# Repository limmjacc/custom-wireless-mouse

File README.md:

# custom-wireless-mouse

Custom BLE wireless mouse: from-scratch PCB (KiCad) and firmware (nRF
Connect SDK / Zephyr) built to fit the mechanical envelope of the Bambu
Lab-style "Wireless Mouse Components Kit-002" (MH002), replacing its two
undocumented/discontinued ICs with fully public, sourceable parts.

See [docs/hardware/README.md](docs/hardware/README.md) for the full design
rationale, bill of materials, and net list, and
[docs/firmware/README.md](docs/firmware/README.md) for firmware scope.

## Layout

```
.
├── hardware/     KiCad 10 project — schematic, PCB layout, libraries
├── firmware/     nRF Connect SDK (Zephyr) application
├── docs/         Design documentation (hardware and firmware)
└── mechanical/   Notes on the reused kit mechanical parts
```

## Status

Schematic complete and ERC-verified (see [docs/hardware/schematic.md](docs/hardware/schematic.md)).
PCB layout not yet started, not built, not tested. No firmware logic has
been written. See each section's open-items document for what's left.

## Credits

Every vendored KiCad library part under `hardware/libraries/vendored/`
carries its own `ATTRIBUTION.md` with full sourcing detail. The two with
licenses other than KiCad's own (CC-BY-SA 4.0, used simply because most
parts were extracted from KiCad's or DigiKey's official libraries):

- The PMW3610DM-SUDU sensor's symbol and footprint, at
  [`hardware/libraries/vendored/pmw3610dm-sudu/`](hardware/libraries/vendored/pmw3610dm-sudu/),
  are from [**siderakb/pmw3610-pcb**](https://github.com/siderakb/pmw3610-pcb),
  an open-hardware PMW3610 breakout board by **siderakb**, licensed under the
  CERN Open Hardware Licence v2 — Permissive (CERN-OHL-P v2).
- The PEC11R rotary encoder footprint and the JS202011SCQN slide switch
  footprint, at
  [`hardware/libraries/vendored/bourns-pec11r/`](hardware/libraries/vendored/bourns-pec11r/)
  and
  [`hardware/libraries/vendored/ck-js202011scqn/`](hardware/libraries/vendored/ck-js202011scqn/),
  are from [**Digi-Key's official KiCad library**](https://github.com/Digi-Key/digikey-kicad-library)
  (CC-BY-SA 4.0).

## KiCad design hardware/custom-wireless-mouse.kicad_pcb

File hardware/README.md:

# Hardware

KiCad 10 project for the custom wireless mouse PCB. Fully self-contained and
portable: every symbol, footprint, and 3D model the schematic depends on is
vendored inside this folder and referenced through `${KIPRJMOD}`-relative
paths — nothing depends on KiCad's global library tables or an internet
connection to open and edit. See [`docs/hardware/schematic.md`](../docs/hardware/schematic.md)
for how the schematic itself is organized.

## Opening the project

Open `custom-wireless-mouse.kicad_pro` in KiCad 10. The project's
`sym-lib-table` and `fp-lib-table` are picked up automatically.

## Layout

```
hardware/
├── custom-wireless-mouse.kicad_pro   Project file
├── custom-wireless-mouse.kicad_sch   Schematic — complete, ERC-clean
├── custom-wireless-mouse.kicad_pcb   PCB layout — not started (no board outline yet)
├── sym-lib-table                     Project-local symbol library table
├── fp-lib-table                      Project-local footprint library table
├── datasheets/                       PDF datasheets for every non-passive part, kebab-case named
├── libraries/
│   ├── local/                        Symbols/footprints authored for this project
│   │   └── symbols/local.kicad_sym     GND, +VSYS, and PWR_FLAG
│   └── vendored/                     One directory per part, each with its own ATTRIBUTION.md
│       ├── nordic-nrf52810-qcxx/       U1 — from KiCad's own official library
│       ├── pmw3610dm-sudu/             U2 — from github.com/siderakb/pmw3610-pcb (CERN-OHL-P v2)
│       ├── ti-tlv61220/                U3 — symbol hand-drawn from TI's datasheet pinout
│       ├── ndk-nx2016sa/               Y1 — from KiCad's own official library
│       ├── bourns-pec11r/              ENC1 — from DigiKey's official KiCad library
│       ├── panasonic-evq-p7b01p/       SW2–SW4 — from KiCad's own official library
│       ├── ck-js202011scqn/            SW1 — from DigiKey's official KiCad library
│       └── samtec-tsw-104-07-t-s/      J1 — from KiCad's own official library
├── fab-outputs/                      Gerbers, drill, pick-and-place, and BOM exports per revision
└── 3d-renders/                       Exported board renders (PNG/STEP) for docs and reference
```

## Library policy

Every specific, individually sourced part (every IC, the crystal, the
encoder, every switch, the header) has its own symbol and footprint vendored
into `libraries/vendored/<part>/` — nothing depends on KiCad's global
libraries for these, since a global library's contents can differ across
KiCad installs and versions. Only truly generic, manufacturer-agnostic
passives (resistors, capacitors, the inductor) use KiCad's bundled `Device`
and footprint libraries directly, since there's no meaningful "sourcing"
decision attached to a 0603 resistor footprint.

Each vendored part's `ATTRIBUTION.md` records exactly where its symbol and
footprint came from and what license applies (mostly CC-BY-SA 4.0, matching
KiCad's own library license, since most of these were extracted from KiCad's
or DigiKey's official libraries; U2 is CERN-OHL-P v2 from its open-hardware
source; U3's symbol is original, hand-drawn from a public datasheet pinout
table rather than copied from anywhere).

## Datasheets

`datasheets/` holds a PDF for every part above the passive-component level —
downloaded from the manufacturer or a stable distributor mirror where a
direct link could be found. A couple of manufacturers' sites (Nordic's full
product specification, one slide-switch datasheet) sit behind bot-protection
that blocked a direct download; where that happened, the BOM notes it and
gives the page to fetch manually instead of a broken/substituted link.

## Fabrication outputs

`fab-outputs/` holds exports generated *from* the KiCad project (Gerbers,
drill files, pick-and-place, BOM) — never hand-edited. Regenerate per
revision; don't rely on stale exports. Nothing has been exported yet since
the PCB layout hasn't started.

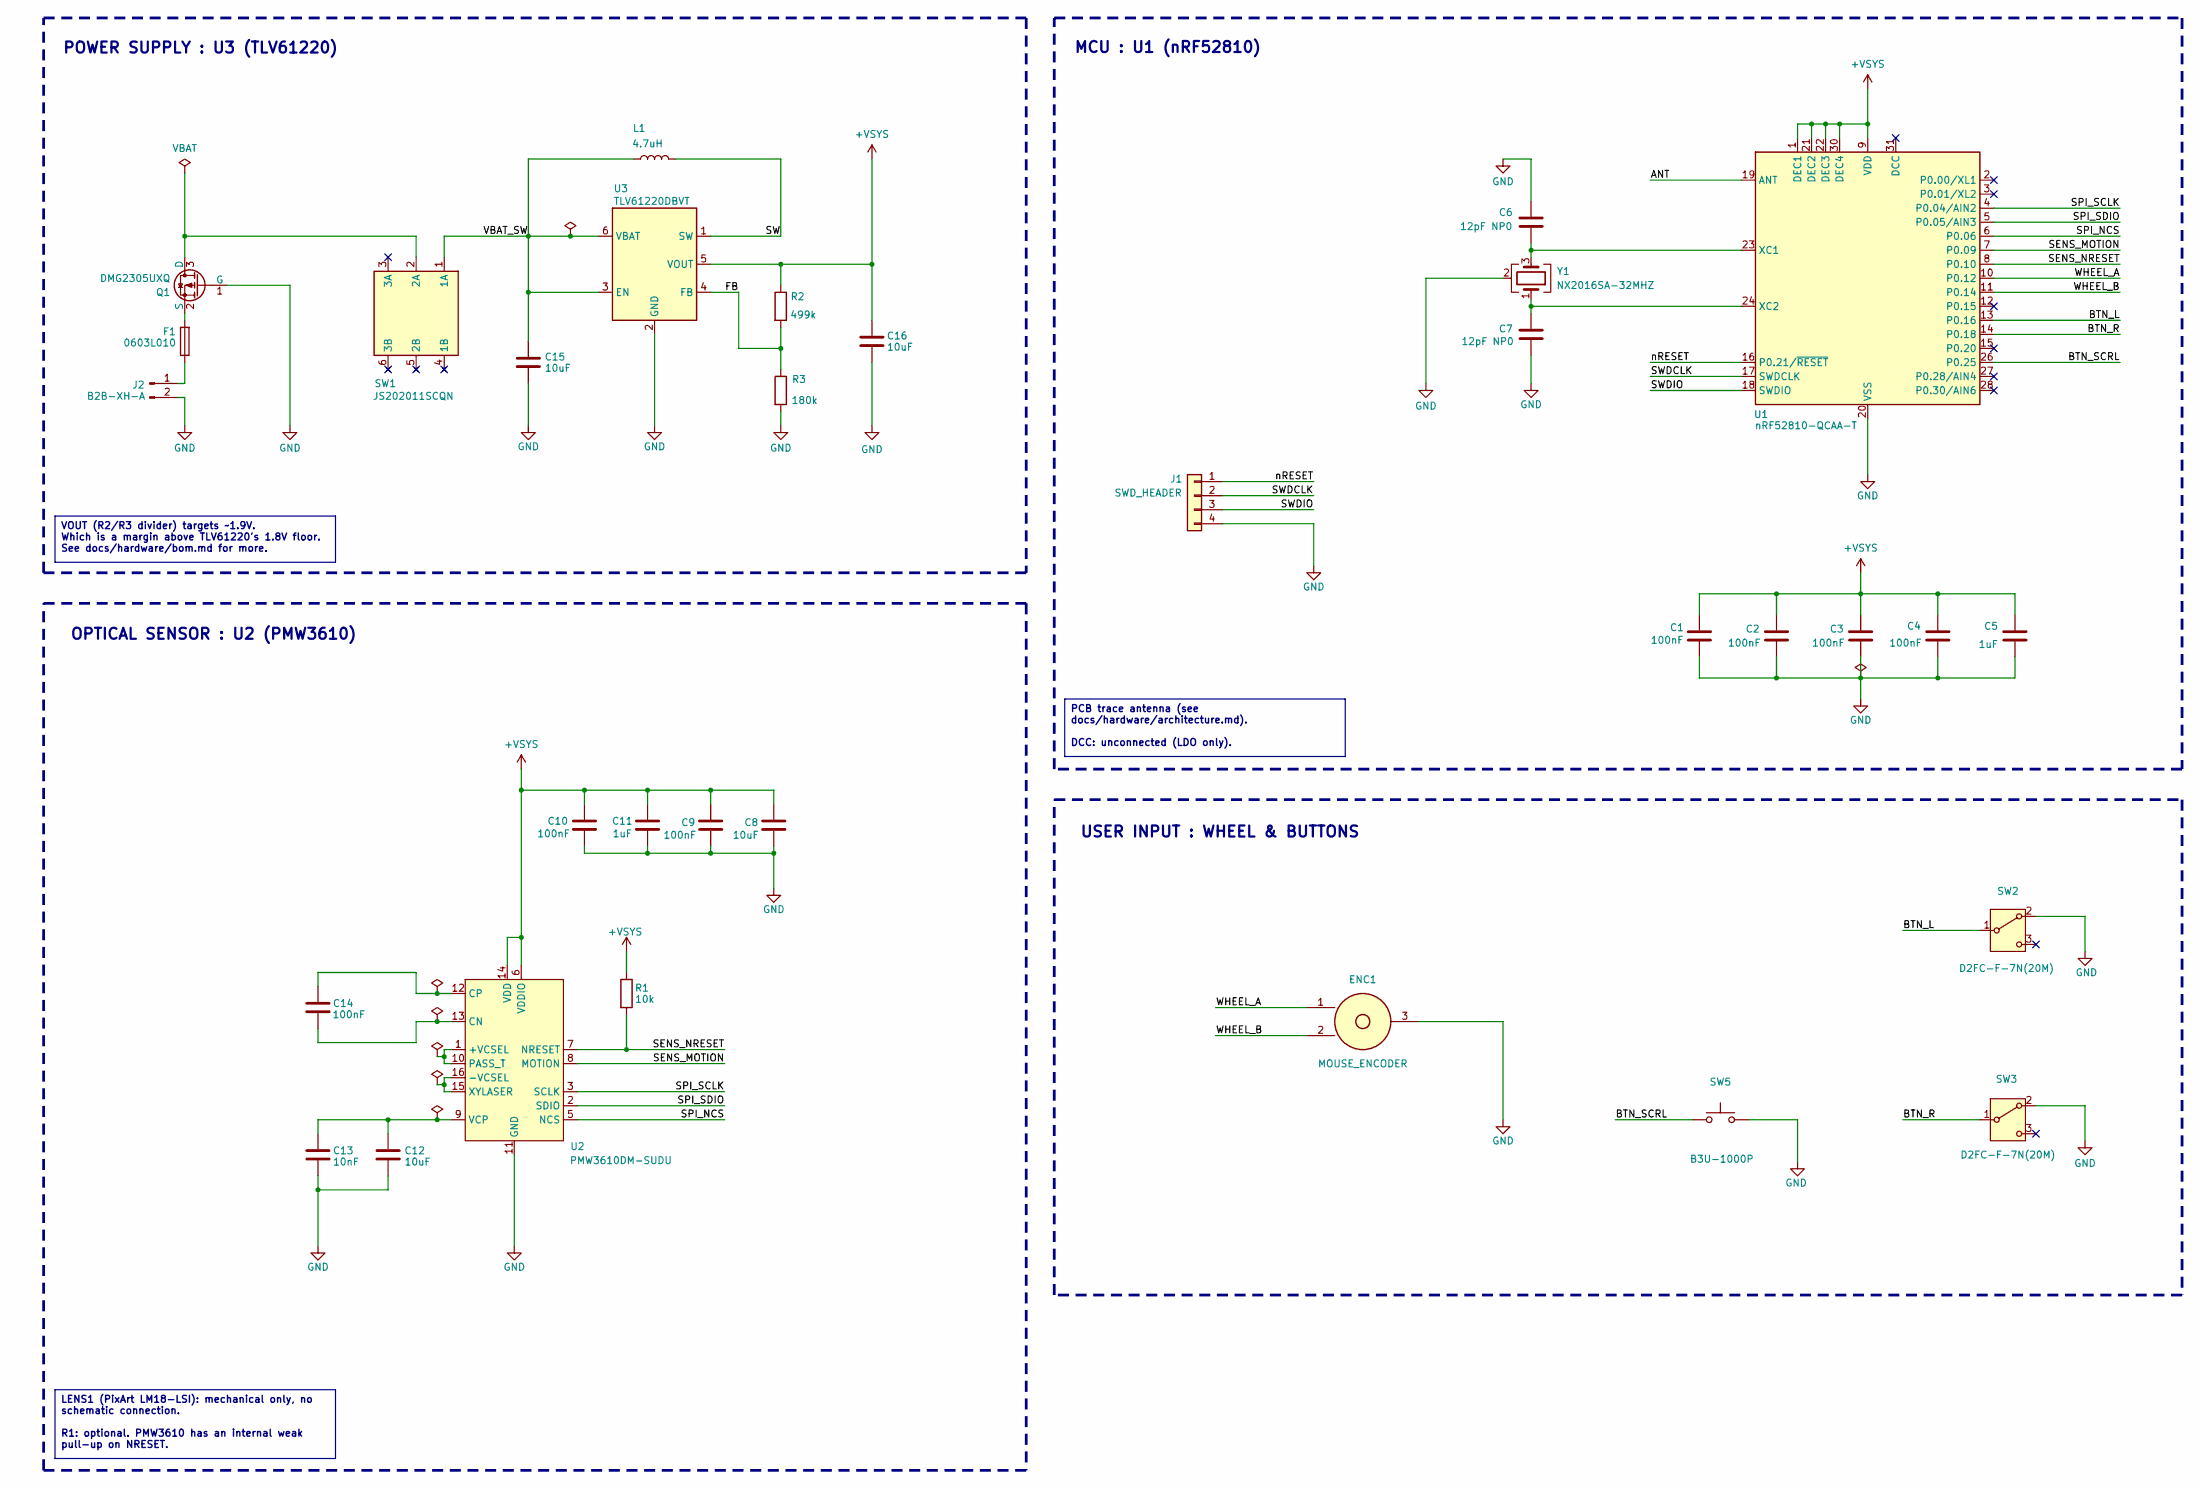
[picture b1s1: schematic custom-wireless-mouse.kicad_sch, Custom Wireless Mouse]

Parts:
C1, C2, C3, C4, C9, C10, C14: 100nF; C_0603_1608Metric; MPN CC0603KRX7R9BB104
C5, C11: 1uF; C_0603_1608Metric; MPN CC0603KRX5R6BB105
C6, C7: 12pF NP0; C_0402_1005Metric; MPN CC0402FRNPO9BN120
C8, C12, C15, C16: 10uF; C_0603_1608Metric; MPN GRT188R61A106KE13J
C13: 10nF; C_0603_1608Metric; MPN CC0603KRX7R9BB103
ENC1: MOUSE_ENCODER; encoder-tht-placeholder-mouse-wheel; MPN Mouse scroll encoder, 7-9mm body height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
F1: 0603L010; fuse-0603-littelfuse-0603l010; MPN 0603L010YR
J1: SWD_HEADER; pinheader-1x04-p2.54mm-vertical; MPN TSW-104-07-T-S
J2: B2B-XH-A; battery-conn-jst-b2b-xh-a; MPN B2B-XH-A(LF)(SN)
L1: 4.7uH; L_1008_2520Metric; MPN 1269AS-H-4R7M=P2
Q1: DMG2305UXQ; sot-23-dmg2305uxq; MPN DMG2305UXQ-7
R1: 10k; R_0603_1608Metric; MPN RC0603FR-0710KL
R2: 499k; R_0603_1608Metric; MPN RC0603FR-07499KL
R3: 180k; R_0603_1608Metric; MPN RC0603FR-07180KL
SW1: JS202011SCQN; switch-slide-js202011scqn; MPN JS202011SCQN
SW2, SW3: D2FC-F-7N(20M); switch-tht-omron-d2fc-f-7n; MPN D2FC-F-7N(20M)
SW5: B3U-1000P; switch-smd-omron-b3u-1000p; MPN B3U-1000P
U1: nRF52810-QCAA-T; qfn-32-1ep-5x5mm-p0.5mm-ep3.6x3.6mm; MPN nRF52810-QCAA-T
U2: PMW3610DM-SUDU; pmw3610dm-sudu-16-pin; MPN PMW3610DM-SUDU
U3: TLV61220DBVT; sot-23-6; MPN TLV61220DBVT
Y1: NX2016SA-32MHZ; crystal-smd-2016-4pin-2.0x1.6mm; MPN NX2016SA-32MHZ-EXS00A-CS06654

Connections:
+VSYS: C1.1, C2.1, C3.1, C4.1, C5.1, C8.1, C9.1, C10.1, C11.1, C16.1, R1.1, R2.1, U1.1 (DEC1), U1.9 (VDD), U1.21 (DEC2), U1.22 (DEC3), U1.25 (VDD), U1.30 (DEC4), U1.32 (VDD), U2.6 (VDDIO), U2.14 (VDD), U3.5 (VOUT)
/ANT: U1.19 (ANT)
/BTN_L: SW2.1 (COM), U1.13 (P0.16)
/BTN_R: SW3.1 (COM), U1.14 (P0.18)
/BTN_SCRL: SW5.1, U1.26 (P0.25)
/FB: R2.2, R3.1, U3.4 (FB)
/SENS_MOTION: U1.7 (P0.09), U2.8 (MOTION)
/SENS_NRESET: R1.2, U1.8 (P0.10), U2.7 (NRESET)
/SPI_NCS: U1.6 (P0.06), U2.5 (NCS)
/SPI_SCLK: U1.4 (P0.04/AIN2), U2.3 (SCLK)
/SPI_SDIO: U1.5 (P0.05/AIN3), U2.2 (SDIO)
/SW: L1.2, U3.1 (SW)
/SWDCLK: J1.2 (SWDCLK), U1.17 (SWDCLK)
/SWDIO: J1.3 (GND), U1.18 (SWDIO)
/VBAT_SW: C15.1, L1.1, SW1.1 (1A), U3.3 (EN), U3.6 (VBAT)
/WHEEL_A: ENC1.1 (A), U1.10 (P0.12)
/WHEEL_B: ENC1.2 (B), U1.11 (P0.14)
/nRESET: J1.1 (SWDIO), U1.16 (P0.21/~RESET)
GND: C1.2, C2.2, C3.2, C4.2, C5.2, C6.1, C7.2, C8.2, C9.2, C10.2, C11.2, C12.2, C13.2, C15.2, C16.2, ENC1.3 (COM), J1.4 (~RESET), J2.2 (-), Q1.1 (G), R3.2, SW2.2 (NO), SW3.2 (NO), SW5.2, U1.20 (VSS), U1.29 (VSS), U1.33 (VSS), U2.11 (GND), U3.2 (GND), Y1.2 (G), Y1.4 (G)
unnamed: F1.1, J2.1 (+)
unnamed: Q1.3 (D), SW1.2 (2A)
unnamed: F1.2, Q1.2 (S)
unnamed: C6.2, U1.23 (XC1), Y1.3
unnamed: C7.1, U1.24 (XC2), Y1.1
unnamed: U2.1 (+VCSEL), U2.10 (PASS_T)
unnamed: U2.15 (XYLASER), U2.16 (-VCSEL)
unnamed: C14.2, U2.13 (CN)
unnamed: C14.1, U2.12 (CP)
unnamed: C12.1, C13.1, U2.9 (VCP)

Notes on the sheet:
USER INPUT : WHEEL & BUTTONS
POWER SUPPLY : U3 (TLV61220)
MCU : U1 (nRF52810)
OPTICAL SENSOR : U2 (PMW3610)
LENS1 (PixArt LM18-LSI): mechanical only, no schematic connection. R1: optional. PMW3610 has an internal weak pull-up on NRESET.
PCB trace antenna (see docs/hardware/architecture.md). DCC: unconnected (LDO only).
VOUT (R2/R3 divider) targets ~1.9V. Which is a margin above TLV61220's 1.8V floor. See docs/hardware/bom.md for more.

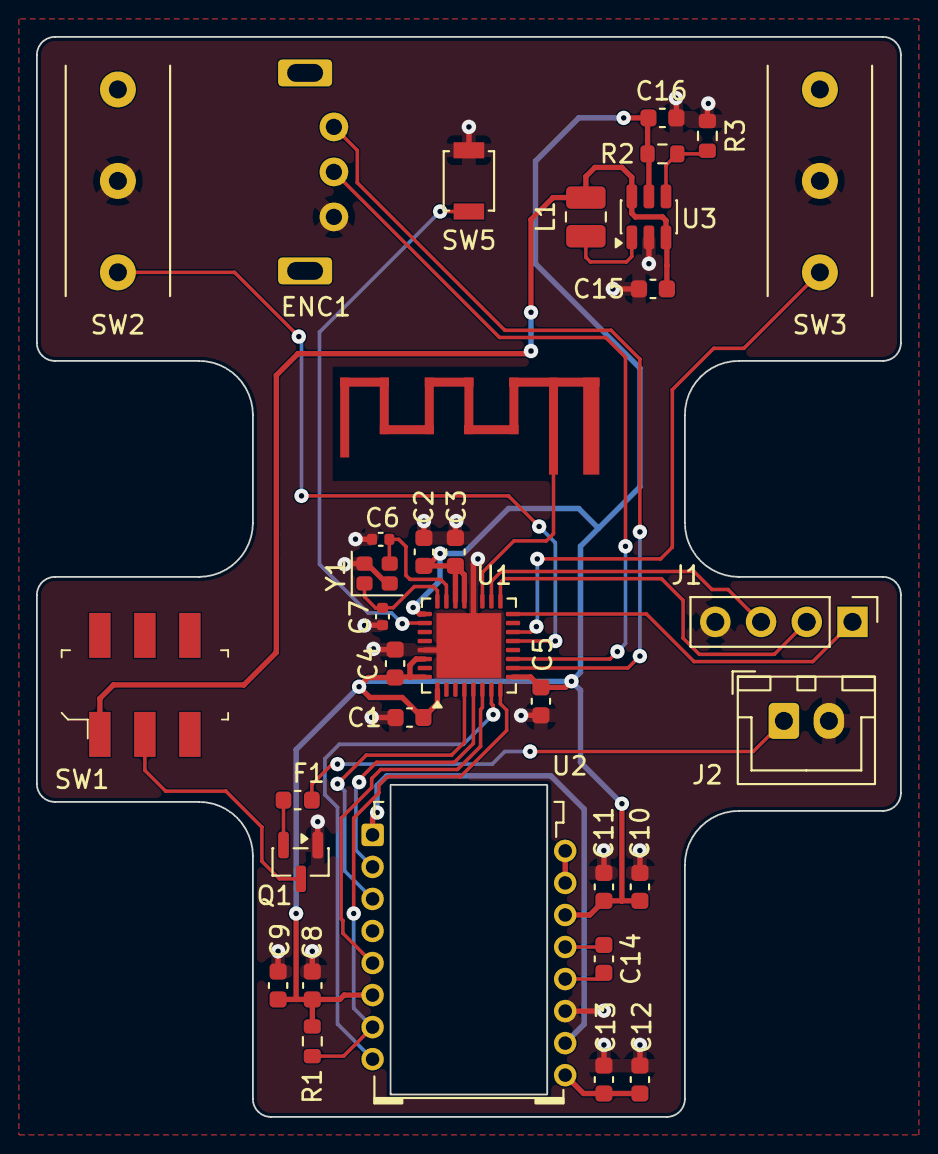
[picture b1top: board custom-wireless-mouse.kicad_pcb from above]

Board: 2 copper layers, 48.0 x 60.0 mm, 33 parts (0 on the bottom side), 28 nets.

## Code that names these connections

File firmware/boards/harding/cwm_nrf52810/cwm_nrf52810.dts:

/*
 * SPDX-License-Identifier: Apache-2.0
 *
 * Board definition for the custom wireless mouse PCB (U1: nRF52810, 32-QFN
 * 5x5mm package). See docs/hardware/ for the full electrical design this
 * board file targets, in particular pinout.md and open-items.md — several
 * peripheral nodes below are deliberately left unassigned pending the GPIO
 * pin assignment open item.
 */

/dts-v1/;
#include <nordic/nrf52810_qfaa.dtsi>
#include "cwm_nrf52810-pinctrl.dtsi"

/ {
	model = "Custom Wireless Mouse (nRF52810)";
	compatible = "harding,cwm-nrf52810";

	chosen {
		zephyr,sram = &sram0;
		zephyr,flash = &flash0;
	};

	/*
	 * Not yet defined here, pending pin assignment
	 * (docs/hardware/open-items.md, item 5):
	 *
	 *   - spi1: bus to U2 (PMW3610), pinctrl for SCLK/SDIO/NCS
	 *     (docs/hardware/pinout.md, U1 section)
	 *   - gpio-keys: BTN_L (SW2), BTN_R (SW3), BTN_FN (SW4), WHEEL_SW
	 *   - PMW3610 MOTION line as a GPIO interrupt input
	 *   - WHEEL_A / WHEEL_B quadrature inputs for ENC1
	 *
	 * Add these once layout fixes the P0.xx assignment for each signal.
	 */
};

/*
 * P0.21 doubles as the SWD RESET line (J1) per
 * docs/hardware/pinout.md — configure it as external reset rather than a
 * general-purpose GPIO.
 */
&uicr {
	gpio-as-nreset;
};

&gpiote {
	status = "okay";
};

&gpio0 {
	status = "okay";
};
